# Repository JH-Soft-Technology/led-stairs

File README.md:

# Ledstairs

Microcontroller operating stairway lighting via motion sensors and light intensity sensor. Has two [PIR motion sensors](https://en.wikipedia.org/wiki/Passive_infrared_sensor) to detect human or animal movement.
The board also has a light sensitivity sensor that prevents from triggering when there is still enough light.

It has been designed to be modularly applied to stairs of different sizes. Individual boards can be joined together and thus the possibility of lighting up the stairs with the number 8/16/24/32 steps.

If for some reason there are fewer steps than 8 or 16 or 24 or 32. It is possible to light up such a number of steps. The required number of slabs is connected and only the number of required steps is involved. In addition, the slots will be empty.

## Schematic

Board has one 12V input terminal. It's different to old version, because the old one has input for 12V and 5V independently. New design has only 12V input and it is redist for inner circuit to 5V voltage.

## Design of the board

Board can be chained with up to 3 others. So maximal light management is 32 steps.

## PCB board

It is double sided PCB board.

Master front side of the board with chips.

Master back side of the board with chips.

Master nad slave boards chained together.

## How does it work

This board is turning on each step by step depends from which side is someone goes. Each step is turn on with little delay so it has nice effect. You can put a 12V LED strips to each step or
small light into the wall next to the each step. It depends on witch stairs you have.

In the feature, I'll put some video or moving picture in GIF format, how does it work.

## What you need to accomplish the project

- 12V power supply with current depends on number of the steps and length of LED strip. You need to calculate total current drain of all LED strips plus 25% extra for safe power supply operation.

Example:

```
You have 16 steps and each step has 70 cm long LED strip.
1m of led strip need 4,2 watts.

16 x 0,7 = 11,2m LED strip.

11,2 x 4,2 = 47,02 watts to all LED strips.

You need add 25% from 47,02 which is 58,75 watts.

So you need to by powers supply with 12V voltage and at least 60 watts. 60 watts for 12V power supply is 5 amps.
```

- 2 PIR sensor like [HC-SR501](https://www.amazon.com/HC-SR501/s?k=HC-SR501)
- A cable with two wires init. A cable cross section of at least 0,25 mm to each.
- Some 12V LED strips or lights at 12V.
- Some case for microcontroller and power supply.

## Visual

## Authors

- **Jiří Horálek** - _Initial work_ - [jhoralek](https://github.com/jhoralek)

## License

This project is licensed under the MIT License - see the [LICENSE](LICENSE) file for details

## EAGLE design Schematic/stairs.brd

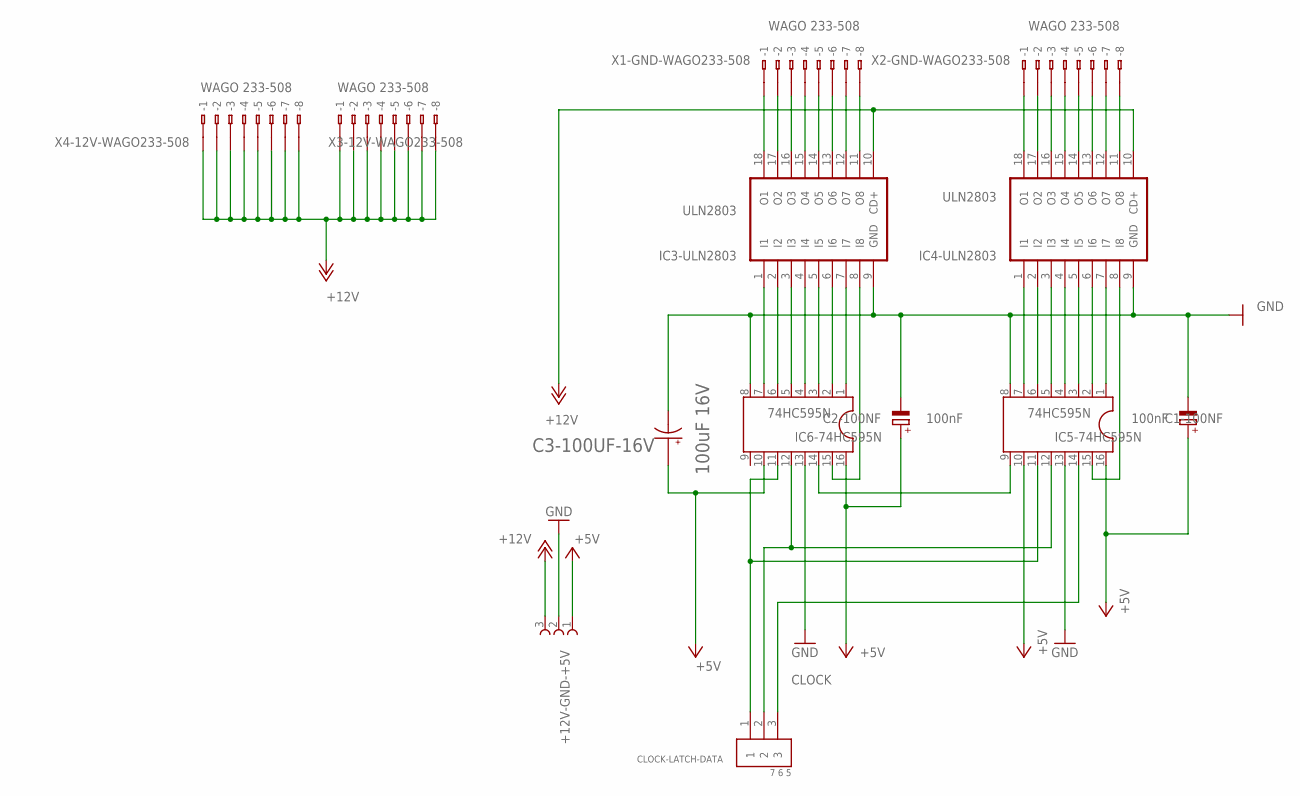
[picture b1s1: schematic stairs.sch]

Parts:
+12V-GND-+5V: +12V GND +5V; 691212710003
C1-100NF, C2-100NF: 100nF; E2,5-6E
C3-100UF-16V: 100uF 16V; CAPPRD200W50D500H1000
CLOCK-LATCH-DATA: 7 6 5; MOLEX_0022272031
IC3-ULN2803, IC4-ULN2803: ULN2803; DIL18
IC5-74HC595N, IC6-74HC595N: 74HC595N; DIL16
X1-GND-WAGO233-508, X2-GND-WAGO233-508, X3-12V-WAGO233-508, X4-12V-WAGO233-508: WAGO 233-508; 233-508

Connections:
+5V: +12V-GND-+5V.1, C1-100NF.+, C2-100NF.+, C3-100UF-16V.1, IC5-74HC595N.10, IC5-74HC595N.16, IC6-74HC595N.10, IC6-74HC595N.16
+12V: +12V-GND-+5V.3, IC3-ULN2803.10 (CD+), IC4-ULN2803.10 (CD+), X3-12V-WAGO233-508.B1 (B-1), X3-12V-WAGO233-508.B2 (B-2), X3-12V-WAGO233-508.B3 (B-3), X3-12V-WAGO233-508.B4 (B-4), X3-12V-WAGO233-508.B5 (B-5), X3-12V-WAGO233-508.B6 (B-6), X3-12V-WAGO233-508.B7 (B-7), X3-12V-WAGO233-508.B8 (B-8), X4-12V-WAGO233-508.B1 (B-1), X4-12V-WAGO233-508.B2 (B-2), X4-12V-WAGO233-508.B3 (B-3), X4-12V-WAGO233-508.B4 (B-4), X4-12V-WAGO233-508.B5 (B-5), X4-12V-WAGO233-508.B6 (B-6), X4-12V-WAGO233-508.B7 (B-7), X4-12V-WAGO233-508.B8 (B-8)
CLOCK: CLOCK-LATCH-DATA.3, IC5-74HC595N.14
GND: +12V-GND-+5V.2, C1-100NF.-, C2-100NF.-, C3-100UF-16V.2 (N), IC3-ULN2803.9 (GND), IC4-ULN2803.9 (GND), IC5-74HC595N.8, IC5-74HC595N.13, IC6-74HC595N.8, IC6-74HC595N.13
unnamed: IC3-ULN2803.8 (I8), IC6-74HC595N.15
unnamed: IC3-ULN2803.1 (I1), IC6-74HC595N.7
unnamed: IC3-ULN2803.2 (I2), IC6-74HC595N.6
unnamed: IC3-ULN2803.3 (I3), IC6-74HC595N.5
unnamed: IC3-ULN2803.4 (I4), IC6-74HC595N.4
unnamed: IC3-ULN2803.5 (I5), IC6-74HC595N.3
unnamed: IC3-ULN2803.6 (I6), IC6-74HC595N.2
unnamed: IC3-ULN2803.7 (I7), IC6-74HC595N.1
unnamed: IC4-ULN2803.1 (I1), IC5-74HC595N.7
unnamed: IC4-ULN2803.2 (I2), IC5-74HC595N.6
unnamed: IC4-ULN2803.3 (I3), IC5-74HC595N.5
unnamed: IC4-ULN2803.4 (I4), IC5-74HC595N.4
unnamed: IC4-ULN2803.5 (I5), IC5-74HC595N.3
unnamed: IC4-ULN2803.6 (I6), IC5-74HC595N.2
unnamed: IC4-ULN2803.7 (I7), IC5-74HC595N.1
unnamed: IC3-ULN2803.18 (O1), X1-GND-WAGO233-508.B1 (B-1)
unnamed: IC3-ULN2803.17 (O2), X1-GND-WAGO233-508.B2 (B-2)
unnamed: IC3-ULN2803.16 (O3), X1-GND-WAGO233-508.B3 (B-3)
unnamed: IC3-ULN2803.15 (O4), X1-GND-WAGO233-508.B4 (B-4)
unnamed: IC3-ULN2803.14 (O5), X1-GND-WAGO233-508.B5 (B-5)
unnamed: IC3-ULN2803.13 (O6), X1-GND-WAGO233-508.B6 (B-6)
unnamed: IC3-ULN2803.12 (O7), X1-GND-WAGO233-508.B7 (B-7)
unnamed: IC3-ULN2803.11 (O8), X1-GND-WAGO233-508.B8 (B-8)
unnamed: IC4-ULN2803.18 (O1), X2-GND-WAGO233-508.B1 (B-1)
unnamed: IC4-ULN2803.17 (O2), X2-GND-WAGO233-508.B2 (B-2)
unnamed: IC4-ULN2803.16 (O3), X2-GND-WAGO233-508.B3 (B-3)
unnamed: IC4-ULN2803.15 (O4), X2-GND-WAGO233-508.B4 (B-4)
unnamed: IC4-ULN2803.14 (O5), X2-GND-WAGO233-508.B5 (B-5)
unnamed: IC4-ULN2803.13 (O6), X2-GND-WAGO233-508.B6 (B-6)
unnamed: IC4-ULN2803.12 (O7), X2-GND-WAGO233-508.B7 (B-7)
unnamed: IC4-ULN2803.11 (O8), X2-GND-WAGO233-508.B8 (B-8)
unnamed: CLOCK-LATCH-DATA.1, IC5-74HC595N.11, IC6-74HC595N.11
unnamed: CLOCK-LATCH-DATA.2, IC5-74HC595N.12, IC6-74HC595N.12
unnamed: IC5-74HC595N.9, IC6-74HC595N.14
unnamed: IC4-ULN2803.8 (I8), IC5-74HC595N.15

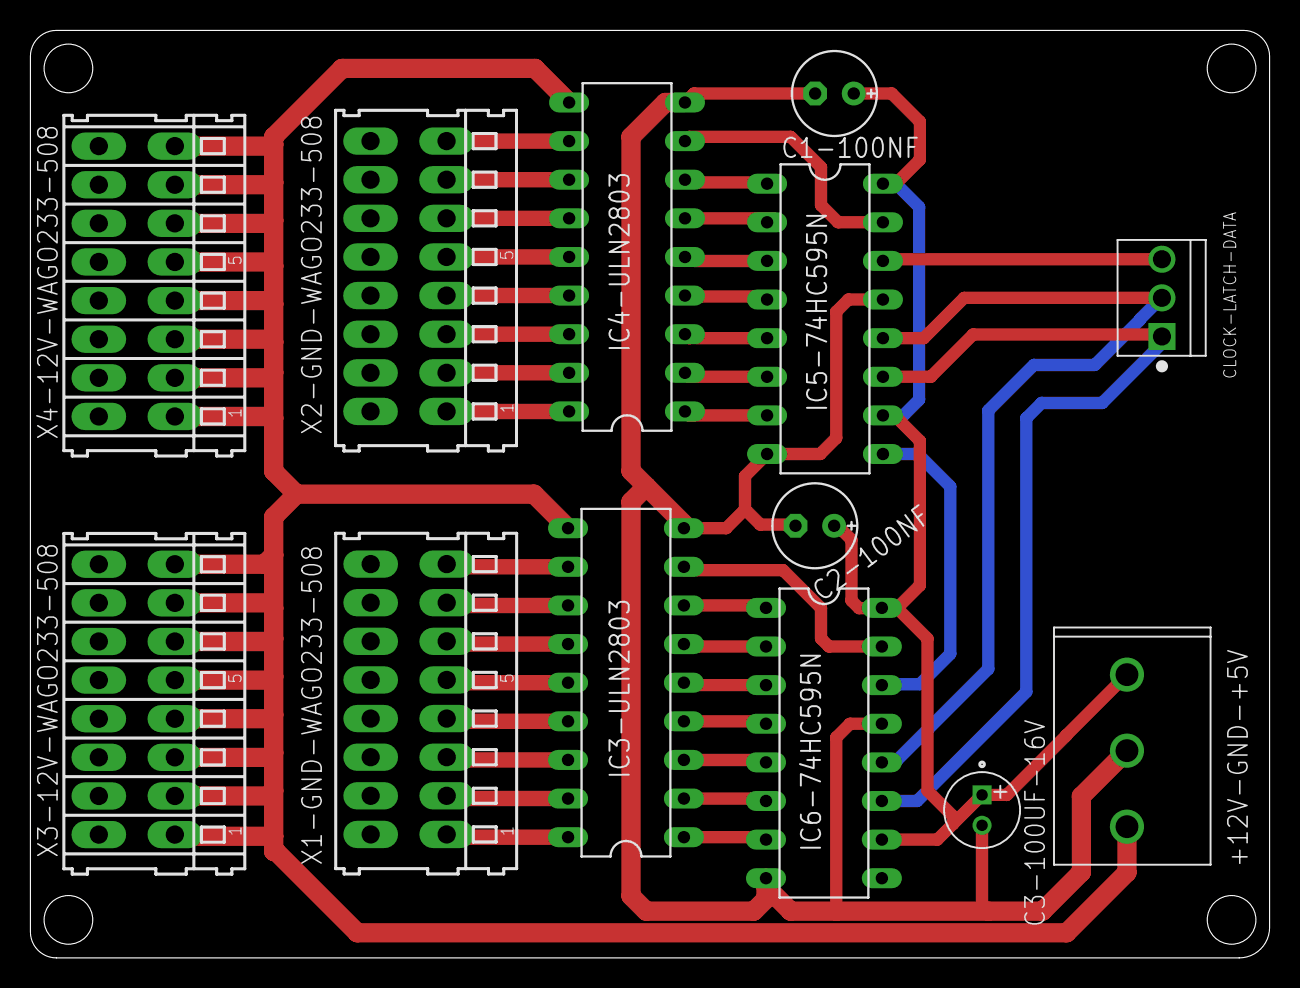
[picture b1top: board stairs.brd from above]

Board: 2 copper layers, 81.5 x 61.0 mm, 13 parts (0 on the bottom side), 39 nets.

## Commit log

2019-01-31 setup a project
2019-01-31 Eagle - schematic and pcb design
2019-01-31 readme file first touch and some gitignore setup
2019-01-31 What you need for project
2019-01-31 another part of readme
2019-01-31 images added
2019-01-31 change image and new readme
2019-01-31 some updates
2019-02-01 update images
2020-01-08 update readme and images
2020-01-08 fix image presentation
2020-01-09 base for board into the wall box
2022-05-10 Update README.md
    typo
